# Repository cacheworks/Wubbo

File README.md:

A wireless 34 key keyboard with the top pinky keys moved to the 6th column.

### [Interactive Bill of materials](https://cacheworks.github.io/Wubbo/)
### [Example ZMK config repo](https://github.com/mveerd/wubbo-zmk-config)

---
__Why move the top pinky keys to the side?__  

 Moving my pinky to the side instead of upwards feels more natural and limits the movement and rotation of my hands on the board.  
This 'pinky cluster' is inspired by boards like [balbuzard](https://github.com/brow/balbuzard) and [osprette](https://github.com/smores56/osprette)

__Who did the silkscreen art?__  
  
All credits for the handdrawn art go to Perce at [madebyperce.com](https://madebyperce.com/)  🙇

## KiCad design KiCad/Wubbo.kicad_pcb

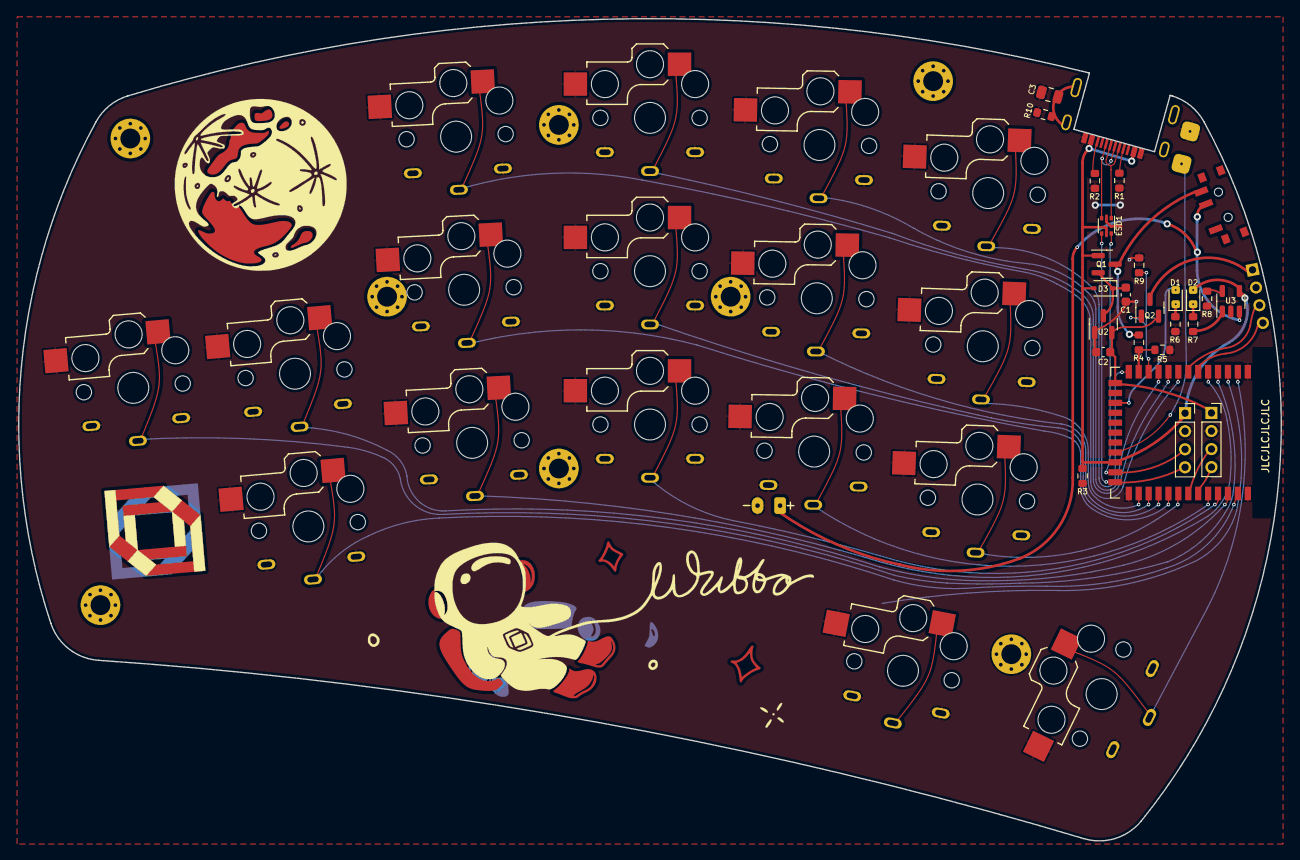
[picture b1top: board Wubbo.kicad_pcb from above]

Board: 2 copper layers, 140.0 x 91.2 mm, 53 parts (1 on the bottom side), 43 nets.

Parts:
C1, C2: 1uF; C_0603_1608Metric
C3: 4.7n; C_0805_2012Metric
D1: Blue LED; LED_0603_1608Metric_shinethrough
D2: Red LED; LED_0603_1608Metric
D3: D_Schottky; D_SOD-323
ESD1: USBLC6-2P6; SOT-666
GR1, GR2: 9b7f651c-c6a4-4f53-b457-ec411c8fc700
GR3: frontright-2
GR4: frontleft-2
GR5: frontright-1
GR6: frontleft-1
J1: USB_C_Receptacle; USB-C-12-Pin-MidMount
J2: SWD; PinSocket_1x04_P2.00mm_Vertical
J3: USB; PinSocket_1x04_P2.00mm_Vertical
J4: JST-BATT; JST_PH_S2B-PH-K_1x02_P2.00mm_Horizontal
J5: USB; PinHeader_1x04_P2.00mm_Vertical
Q1, Q2: AO3407; SOT-23
R1, R2: 5.1K; R_0603_1608Metric
R3: 100K; R_0603_1608Metric
R4: 806/820k; R_0603_1608Metric
R5, R9: 2M; R_0603_1608Metric
R6, R7: 1K; R_0603_1608Metric
R8: 10K; R_0603_1608Metric
R10: 1M; R_0603_1608Metric
R_TACT1: SW_Push; 3-4-2_micro_tact_switch
SW1, SW2, SW3, SW4, SW5, SW6, SW7, SW8, SW9, SW10, SW11, SW12, SW13, SW14, SW15, SW16, SW17: Choc; combined-choc-reversible
SW_POW1: SW_SPDT; SW_SPDT_PCM12
TENT1: Tenting Puck; Tenting_Puck
U1: nRF52840_holyiot_18010
U2: XC6206P LDO; SOT-23
U3: LTC4054ES5-4.2; TSOT-23-5

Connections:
+3V3: C2.1, J2.1, Q2.2 (S), U1.14 (VDD_nRF), U2.2 (VO)
+BATT: J4.1, SW_POW1.2 (B), U3.3 (BAT)
/BAT+_SWITCHED: Q1.3 (D), R4.1, SW_POW1.3 (C)
/Net-(U3-PROG): R8.2, U3.5 (PROG)
/V-IN: C1.1, D3.1 (K), Q1.2 (S), U2.3 (VI)
BLUE_LED: D1.2 (A), U1.16 (P1.09)
D+: ESD1.4 (I/O2), J3.4, U1.24 (D+)
D-: ESD1.6 (I/O1), J3.3, U1.23 (D-)
EXT_VCC: J5.1, Q2.3 (D)
Earth: C3.2, J1.S1 (SHIELD), R10.2
GND: C1.2, C2.2, C3.1, ESD1.2 (GND), J1.A1 (GND), J2.2, J3.2, J4.2, J5.2, R1.2, R2.2, R3.2, R5.2, R6.2, R8.1, R9.2, R10.1, R_TACT1.2, SW1.2, SW2.2, SW3.2, SW4.2, SW5.2, SW6.2, SW7.2, SW8.2, SW9.2, SW10.2, SW11.2, SW12.2, SW13.2, SW14.2, SW15.2, SW16.2, SW17.2, U1.1 (GND), U1.25 (GND), U1.37 (GND), U2.1 (GND), U3.2 (GND)
unnamed: D1.1 (K), R6.1
unnamed: D2.1 (K), R7.1
unnamed: J1.A5 (CC1), R1.1
unnamed: J1.B5 (CC2), R2.1
unnamed: R7.2, U3.1 (~CHRG)
P0.02: J5.3, U1.7 (P0.02)
P0.03: J5.4, U1.6 (P0.03)
RESET: R_TACT1.1, U1.21 (P0.18/RESET)
SW1: SW1.1, U1.4 (P1.13)
SW2: SW2.1, U1.8 (P0.28)
SW3: SW3.1, U1.9 (P0.29)
SW4: SW4.1, U1.10 (P0.30)
SW5: SW5.1, U1.13 (P0.05)
SW6: SW6.1, U1.35 (P0.09)
SW7: SW7.1, U1.29 (P1.01)
SW8: SW8.1, U1.28 (P1.03)
SW9: SW9.1, U1.27 (P1.00)
SW10: SW10.1, U1.26 (P0.22)
SW11: SW11.1, U1.36 (P0.10)
SW12: SW12.1, U1.5 (P1.15)
SW13: SW13.1, U1.34 (P1.06)
SW14: SW14.1, U1.33 (P1.04)
SW15: SW15.1, U1.30 (P1.02)
SW16: SW16.1, U1.3 (P1.10)
SW17: SW17.1, U1.2 (P1.11)
SWDCLK: J2.3, U1.31 (SWDCLK)
SWDIO: J2.4, U1.32 (SWDIO)
USBD+: ESD1.3 (I/O2), J1.A6 (D+), J1.B6 (D+)
USBD-: ESD1.1 (I/O1), J1.A7 (D-), J1.B7 (D-)
VBUS: D2.2 (A), D3.2 (A), ESD1.5 (VBUS), J1.A4 (VBUS), J3.1, Q1.1 (G), R3.1, U1.22 (VBUS), U3.4 (VCC)
VCC_CONTROL: Q2.1 (G), R9.1, U1.11 (P0.31)
VSENSE: R4.2, R5.1, U1.12 (P0.04)

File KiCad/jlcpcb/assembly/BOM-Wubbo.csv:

Comment,Designator,Footprint,LCSC
SW_SPDT,SW_POW1,SW_SPDT_PCM12,C128955
1uF,"C1,C2",C_0603_1608Metric,C15849
4.7n,C3,C_0805_2012Metric,C1744
AO3407,"Q1,Q2",SOT-23,C181093
D_Schottky,D3,D_SOD-323,C191023
1K,"R6,R7",R_0603_1608Metric,C21190
1M,R10,R_0603_1608Metric,C22935
2M,"R5,R9",R_0603_1608Metric,C22976
5.1K,"R1,R2",R_0603_1608Metric,C23186
100K,R3,R_0603_1608Metric,C25803
10K,R8,R_0603_1608Metric,C25804
USBLC6-2P6,ESD1,SOT-666,C2827693
LTC4054ES5-4.2,U3,TSOT-23-5,C32574
806/820k,R4,R_0603_1608Metric,C53198
XC6206P LDO,U2,SOT-23,C5446

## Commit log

2021-11-24 Initial commit (wip)
2022-01-12 WIP PCB
2022-04-12 remove rotary encoder from schematic
2022-04-14 Bump minimist from 1.2.5 to 1.2.6 in /ergogen
    Bumps [minimist](https://github.com/substack/minimist) from 1.2.5 to 1.2.6.
    - [Release notes](https://github.com/substack/minimist/releases)
    - [Commits](https://github.com/substack/minimist/compare/1.2.5...1.2.6)
    ---
    updated-dependencies:
    - dependency-name: minimist
2022-05-03 v0.2
2022-05-03 Add README banner
2022-05-10 Hotswap WIP
2022-06-03 V0.3
2022-07-31 Add BOM / POS files
2022-07-31 Remove vO.2 3d files
2022-07-31 Update gerbers
